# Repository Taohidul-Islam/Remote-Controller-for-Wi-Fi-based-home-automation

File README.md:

9<h1>This is a Wi-Fi Based Remote Controller</h1>
<h2>The remote controller is specifically made for my previous project<a href="https://github.com/Taohidul-Islam/Wi-Fi-Based-Home-Automation"> Wi-Fi-Based-Home-Automation</a></h2>
<p>The remote controller has a thin form factor of 15mm. It uses a wesmos D1 mini as an MCU, a 3.7V Li-ion battery, TP4056 module(type-c) to charge the battery, and a TPS6123 module.<br>
It also does have a debug LED.</p>
<p>The keypad used in the remote is a membrane 4 by 4 matrix. Clicking specific button suck as numeric 1 to 8 gives specific http requests to a webserver hosted on the home automation. Then the server toggles respective switches from on to off or off to on. A, B, C, D and other keys are for extra functions such as display changer, reset buttons or led indicator toggler, firmware update requester for Home Automation etc. The remote controller is a accessory for the home automations device. </p>
<p>The remote can it's own update via OTA.
<h3>KeyMap</h3>
  <p>1---> Toggles Relay 1<br>
     2---> Toggles Relay 2<br>
     3---> Toggles Relay 3<br>
     4---> Toggles Relay 4<br>
     5---> Toggles Relay 5<br>
     6---> Toggles Relay 6<br>
     7---> Toggles Relay 7<br>
     8---> Toggles Relay 8<br>
     9---> Increase people count by one. <br>
     0---> Decrease people count by one. <br>
     A---> Changes display output and keeps the screen still<br>
     B---> Changes display output and keeps the screen switching<br>
     C---> Toggles LED indicator<br>
     D---> Toggles all relays at once.<br>
     *, 0, 9 simountaniously---> Resets Home Automation. <br>
     *, 0, 1 Simountaniously---> Request Home Automation to seek for updates. <br>
     #, 0, 1 Simountaniously---> Request the remote controller to seek for updates. <br>

  </p>
  
<p>The remote has a very compact form factor of about 7 by 7 by 2 cm. And it eradicates the direction problem we face with IR remotes.</p>

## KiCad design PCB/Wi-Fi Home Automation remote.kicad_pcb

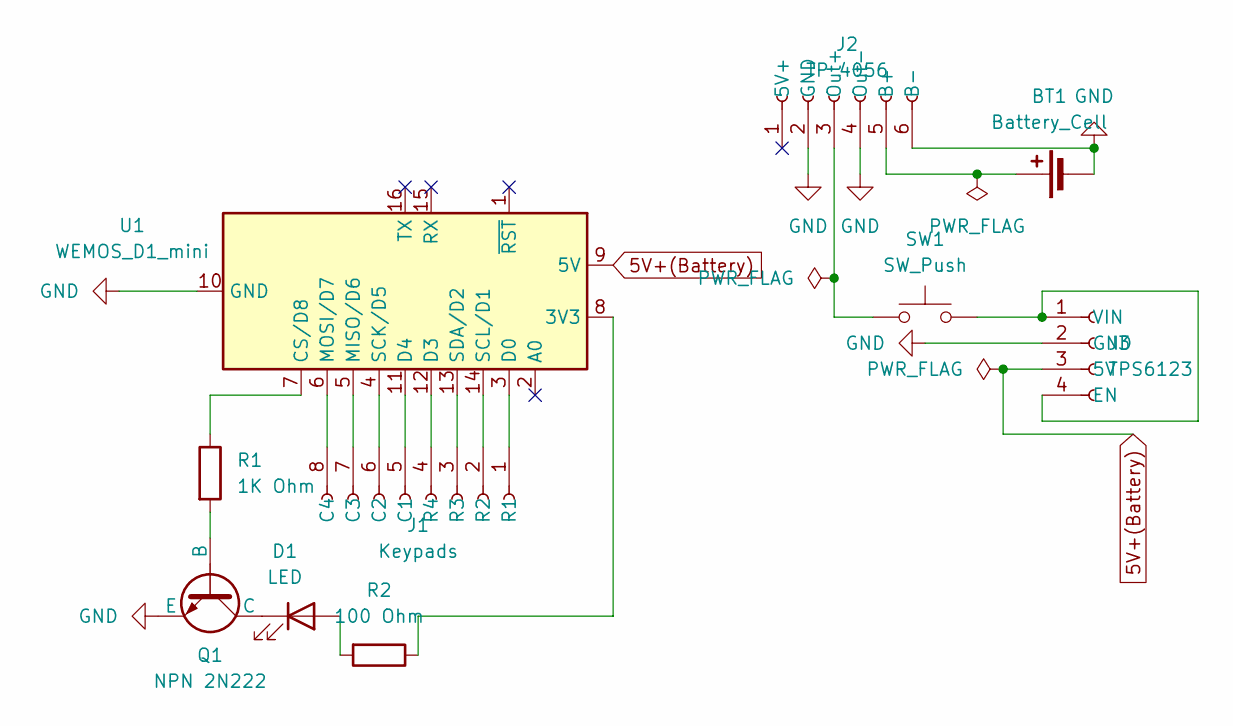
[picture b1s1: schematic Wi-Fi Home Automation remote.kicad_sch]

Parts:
BT1: Battery_Cell; JST_PH_B2B-PH-K_1x02_P2.00mm_Vertical
D1: LED; LED_D3.0mm
J1: Keypads; PinHeader_1x08_P2.54mm_Vertical
J2: TP 4056; TP4056-18650
J3: TPS6123; TPS61023 Module
Q1: NPN 2N222; TO-92_Inline
R1: 1K Ohm; R_Axial_DIN0207_L6.3mm_D2.5mm_P2.54mm_Vertical
R2: 100 Ohm; R_Axial_DIN0207_L6.3mm_D2.5mm_P2.54mm_Vertical
SW1: SW_Push; JST_PH_B2B-PH-K_1x02_P2.00mm_Vertical
U1: WEMOS_D1_mini; WEMOS_D1_mini_light

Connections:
5V+(Battery): J3.3 (5V), U1.9 (5V)
GND: BT1.2 (-), J2.2 (GND), J2.4 (Out-), J2.6 (B-), J3.2 (GND), Q1.3 (E), U1.10 (GND)
unnamed: BT1.1 (+), J2.5 (B+)
unnamed: D1.2 (A), R2.2
unnamed: D1.1 (K), Q1.1 (C)
unnamed: J1.5 (C1), U1.11 (D4)
unnamed: J1.6 (C2), U1.4 (SCK/D5)
unnamed: J1.7 (C3), U1.5 (MISO/D6)
unnamed: J1.8 (C4), U1.6 (MOSI/D7)
unnamed: J1.1 (R1), U1.3 (D0)
unnamed: J1.2 (R2), U1.14 (SCL/D1)
unnamed: J1.3 (R3), U1.13 (SDA/D2)
unnamed: J1.4 (R4), U1.12 (D3)
unnamed: J2.3 (Out+), SW1.1
unnamed: J3.1 (VIN), J3.4 (EN), SW1.2
unnamed: Q1.2 (B), R1.2
unnamed: R2.1, U1.8 (3V3)
unnamed: R1.1, U1.7 (CS/D8)

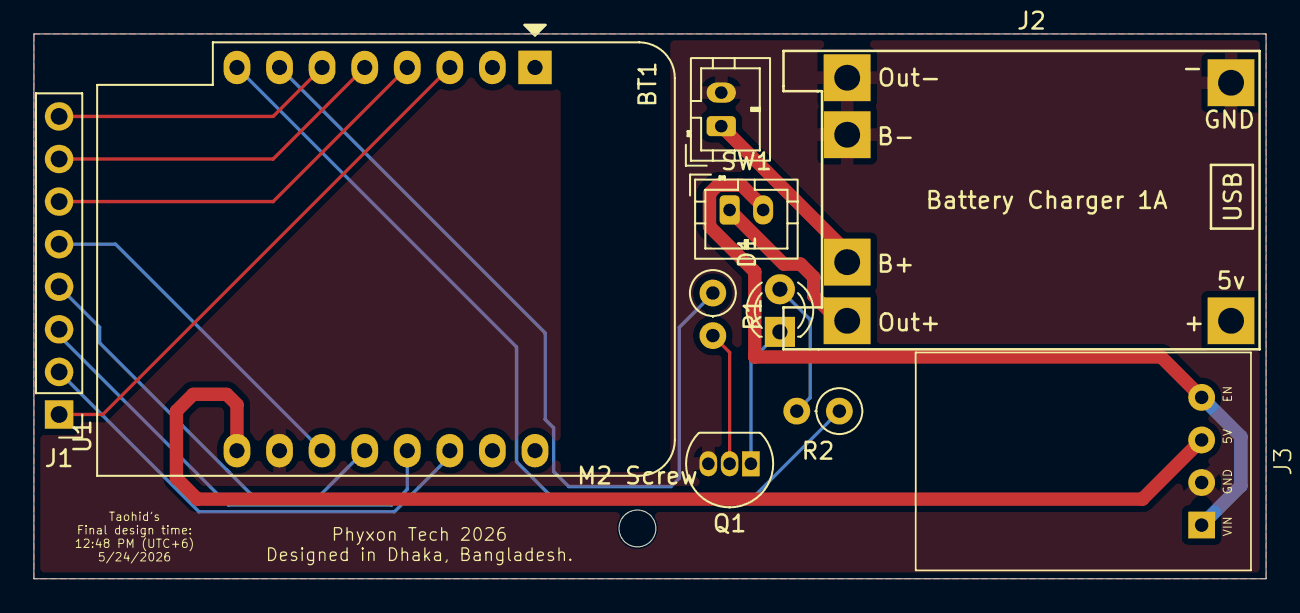
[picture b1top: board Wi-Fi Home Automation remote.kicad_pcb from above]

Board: 2 copper layers, 73.5 x 32.5 mm, 11 parts (0 on the bottom side), 18 nets.

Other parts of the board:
M2 Screw: MountingHole_2.2mm_M2

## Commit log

2026-05-23 Create temp
2026-05-29 Add license information to LISENSE file
2026-06-02 Add images to README for better visualization
    Added images to enhance the project description.
2026-06-14 Enhance README with keypad and design details
    Added details about the keypad functionality and compact design of the remote controller.
2026-06-14 Add Onshape link to 3D model directory
2026-06-14 Revise keypad functionality description in README
    Updated the description of the keypad functionality and clarified the HTTP request handling.
2026-06-16 Add commands for increasing and decreasing people count
2026-06-16 Change firmware version to v2.2 and update OTA IP
    Updated firmware version from 3.0 to 2.2 and modified OTA server IP.
